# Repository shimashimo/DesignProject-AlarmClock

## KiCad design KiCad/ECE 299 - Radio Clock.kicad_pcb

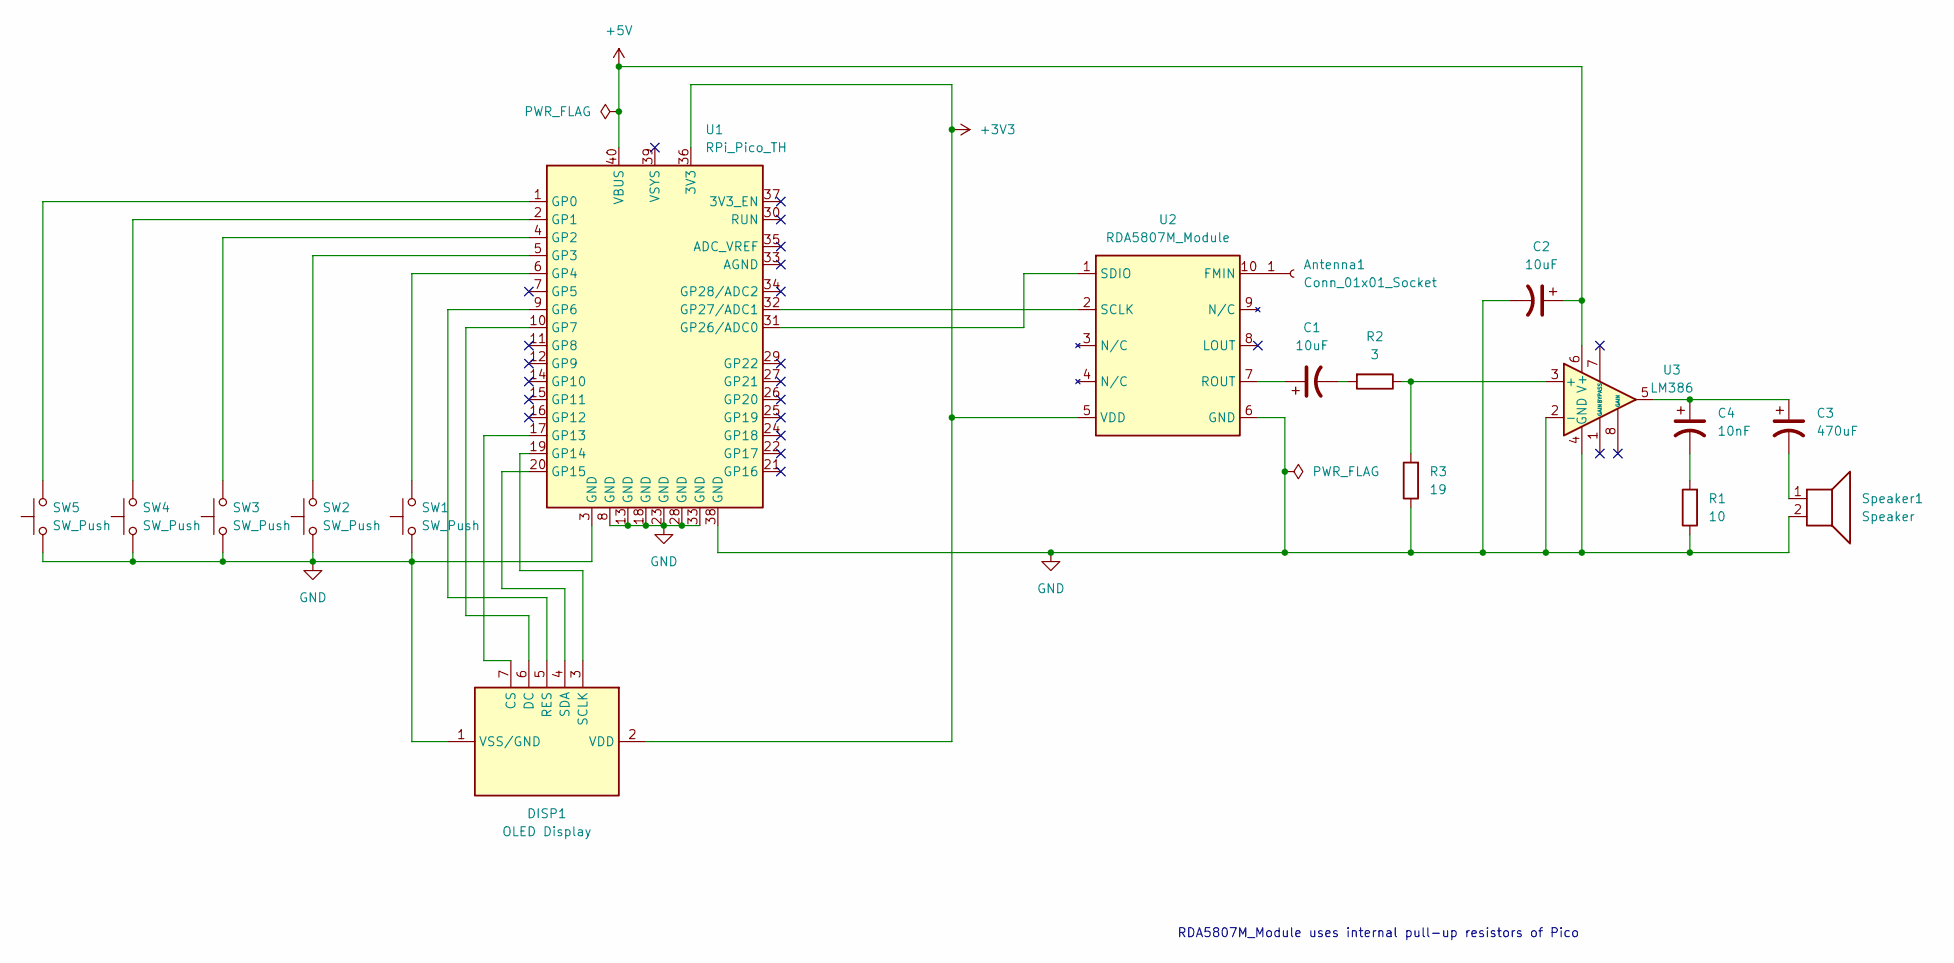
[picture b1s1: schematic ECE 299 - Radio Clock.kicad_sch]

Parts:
Antenna1: Conn_01x01_Socket; PinSocket_1x01_P1.27mm_Vertical
C1, C2: 10uF; CP_Radial_D6.3mm_P2.50mm
C3: 470uF; CP_Radial_D6.3mm_P2.50mm
C4: 10nF; C_Axial_L3.8mm_D2.6mm_P7.50mm_Horizontal
DISP1: OLED Display; OLED_Display_1.3
R1: 10; R_Axial_DIN0207_L6.3mm_D2.5mm_P10.16mm_Horizontal
R2: 3; R_Axial_DIN0207_L6.3mm_D2.5mm_P10.16mm_Horizontal
R3: 19; R_Axial_DIN0207_L6.3mm_D2.5mm_P10.16mm_Horizontal
SW1, SW2, SW3, SW4, SW5: SW_Push; SW_PUSH_6mm
Speaker1: Speaker; TerminalBlock_Phoenix_MKDS-1,5-2_1x02_P5.00mm_Horizontal
U1: RPi_Pico_TH
U2: RDA5807M_Module; RDA5807M_Module_TH
U3: LM386; DIP-8_W7.62mm

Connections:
+3V3: DISP1.2 (VDD), U1.36 (3V3), U2.5 (VDD)
+5V: C2.1, U1.40 (VBUS), U3.6 (V+)
GND: C2.2, DISP1.1 (VSS/GND), R1.1, R3.1, SW1.1, SW2.1, SW3.1, SW4.1, SW5.1, Speaker1.2, U1.3 (GND), U1.8 (GND), U1.13 (GND), U1.18 (GND), U1.23 (GND), U1.28 (GND), U1.33 (GND), U1.38 (GND), U2.6 (GND), U3.2 (-), U3.4 (GND)
unnamed: Antenna1.1, U2.10 (FMIN)
unnamed: C1.2, R2.2
unnamed: C3.1, C4.1, U3.5
unnamed: C3.2, Speaker1.1
unnamed: C4.2, R1.2
unnamed: DISP1.7 (CS), U1.17 (GP13)
unnamed: DISP1.6 (DC), U1.10 (GP7)
unnamed: DISP1.5 (RES), U1.9 (GP6)
unnamed: DISP1.3 (SCLK), U1.19 (GP14)
unnamed: DISP1.4 (SDA), U1.20 (GP15)
unnamed: SW5.2, U1.1 (GP0)
unnamed: SW4.2, U1.2 (GP1)
unnamed: SW3.2, U1.4 (GP2)
unnamed: SW2.2, U1.5 (GP3)
unnamed: SW1.2, U1.6 (GP4)
unnamed: U1.31 (GP26/ADC0), U2.1 (SDIO)
unnamed: U1.32 (GP27/ADC1), U2.2 (SCLK)
unnamed: C1.1, U2.7 (ROUT)
unnamed: R2.1, R3.2, U3.3 (+)

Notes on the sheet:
RDA5807M_Module uses internal pull-up resistors of Pico

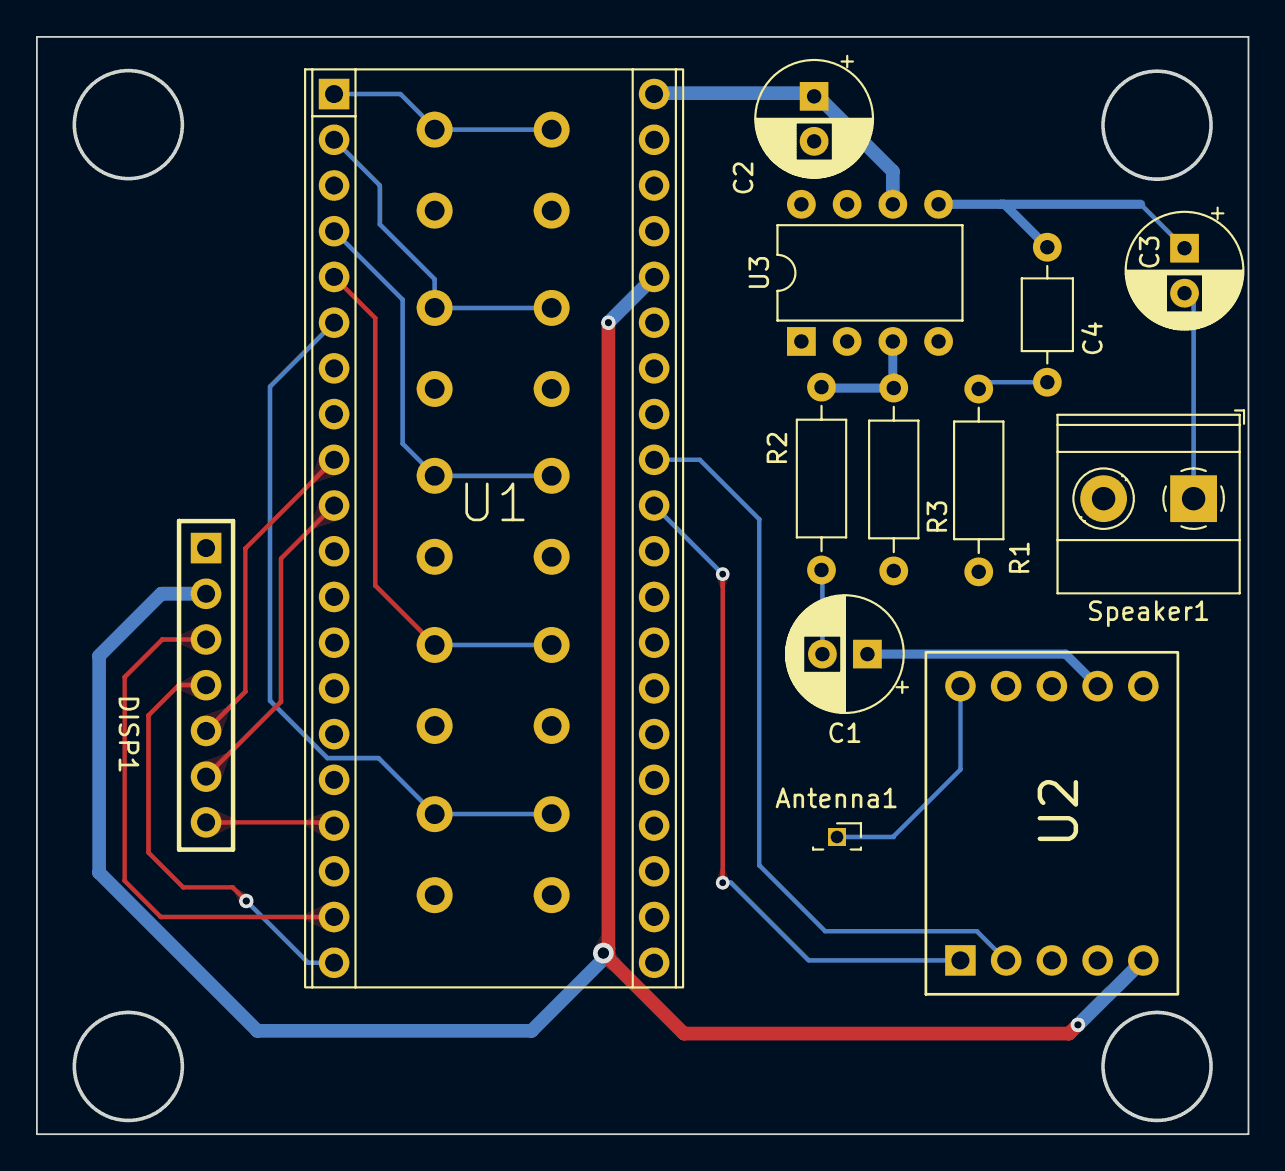
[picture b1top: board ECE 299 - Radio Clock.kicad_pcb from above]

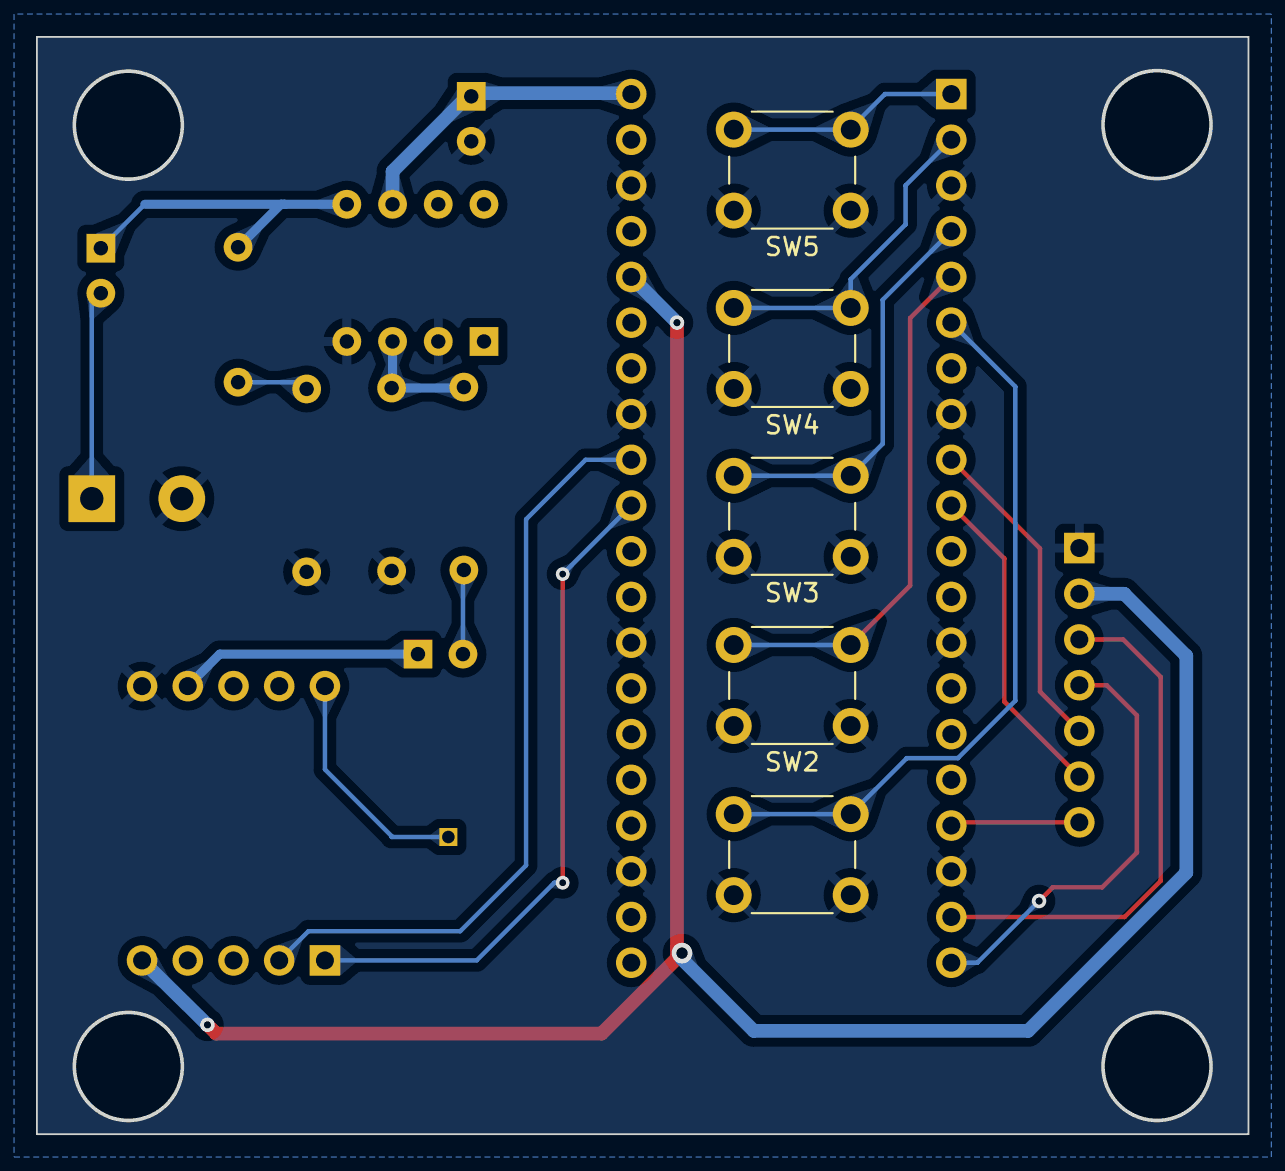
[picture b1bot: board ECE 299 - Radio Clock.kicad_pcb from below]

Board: 2 copper layers, 67.2 x 60.9 mm, 18 parts (5 on the bottom side), 22 nets.

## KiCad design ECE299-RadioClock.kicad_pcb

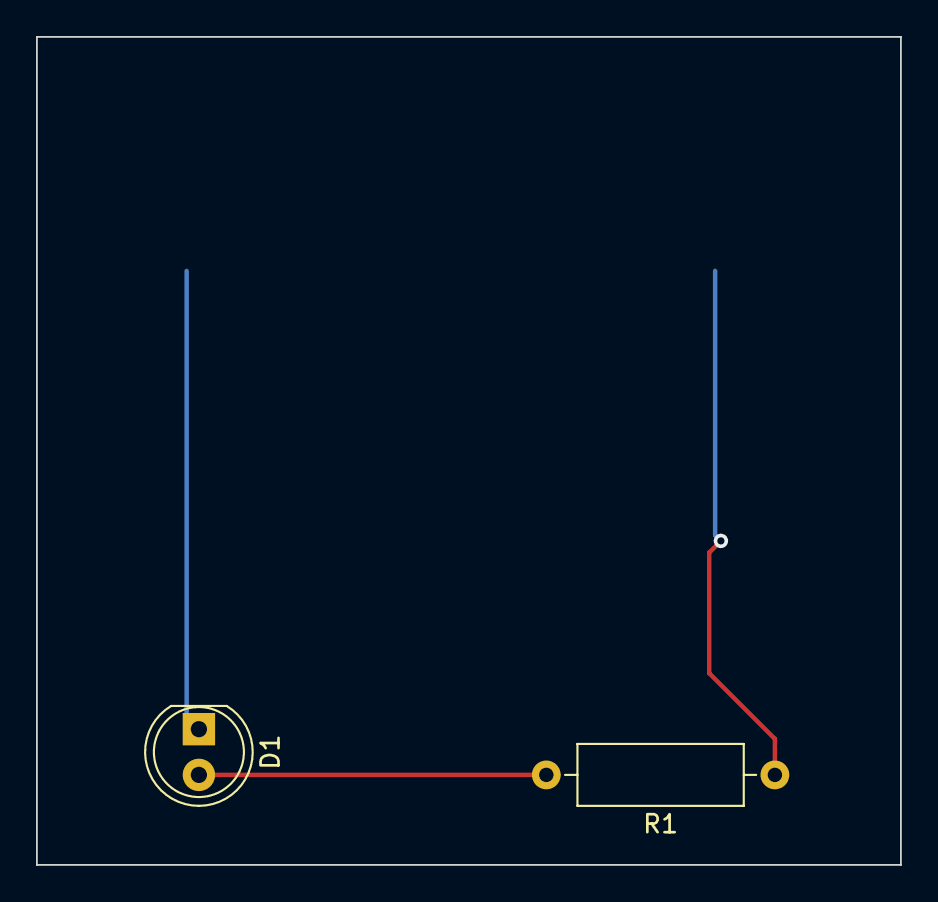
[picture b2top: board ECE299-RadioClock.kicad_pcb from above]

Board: 2 copper layers, 48.0 x 46.0 mm, 3 parts (1 on the bottom side), 3 nets.

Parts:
BT1: 3V; BatteryHolder_Keystone_1058_1x2032
D1: RED; LED_D5.0mm
R1: 1k; R_Axial_DIN0309_L9.0mm_D3.2mm_P12.70mm_Horizontal

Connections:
/led: D1.2 (A), R1.2
GND: BT1.2 (-), D1.1 (K)
VCC: BT1.1 (+), R1.1

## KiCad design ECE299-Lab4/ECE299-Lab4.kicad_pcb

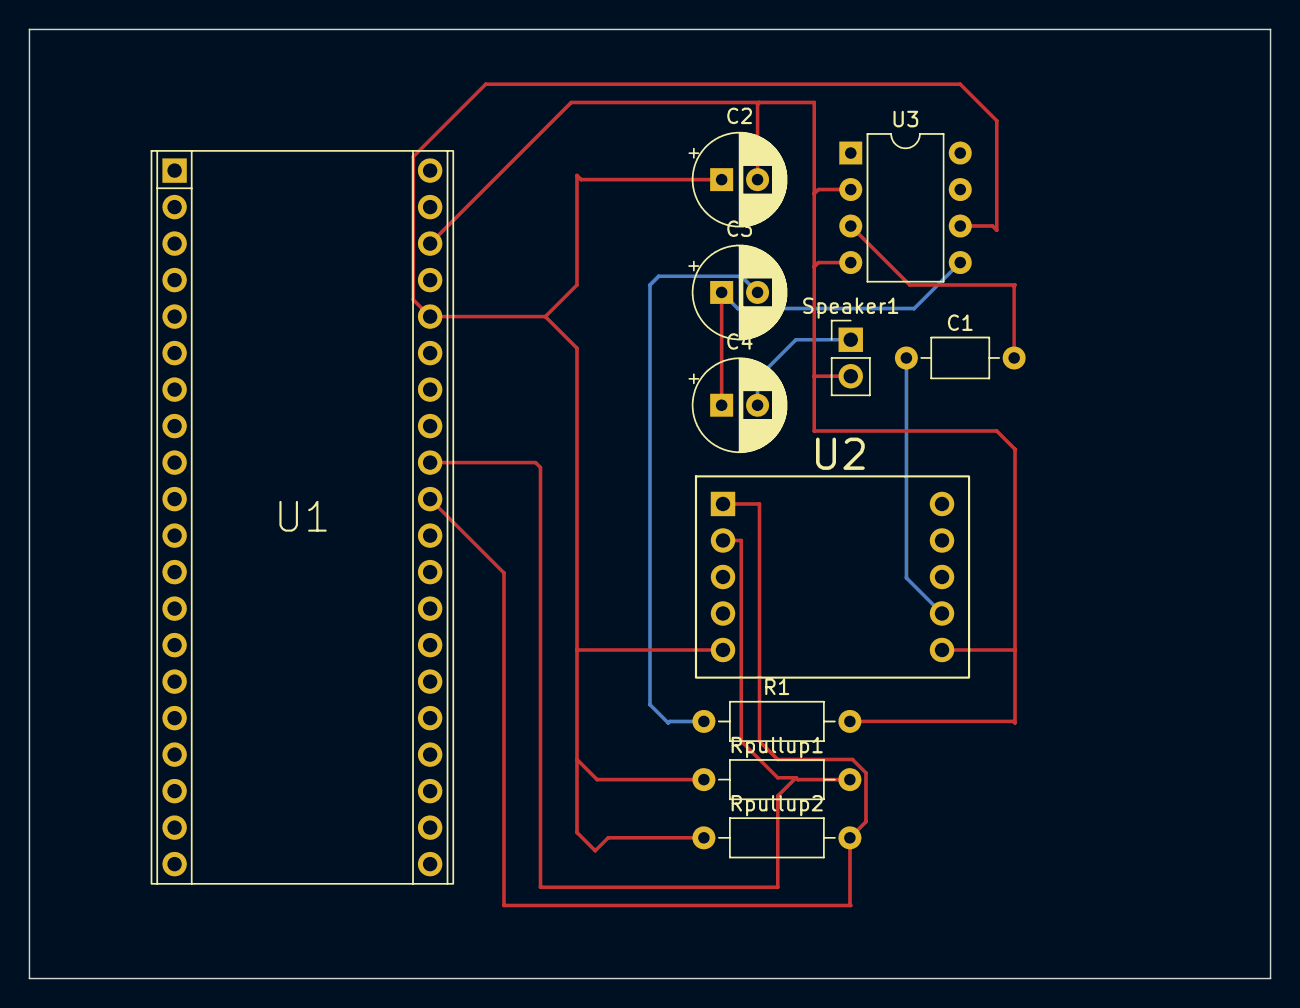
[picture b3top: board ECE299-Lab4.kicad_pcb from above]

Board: 2 copper layers, 86.4 x 66.0 mm, 11 parts (0 on the bottom side), 9 nets.

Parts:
C1: 10nF; C_Axial_L3.8mm_D2.6mm_P7.50mm_Horizontal
C2, C3: 10uF; CP_Radial_D6.3mm_P2.50mm
C4: 470uF; CP_Radial_D6.3mm_P2.50mm
R1: 10; R_Axial_DIN0207_L6.3mm_D2.5mm_P10.16mm_Horizontal
Rpullup1, Rpullup2: 2k; R_Axial_DIN0207_L6.3mm_D2.5mm_P10.16mm_Horizontal
Speaker1: 8; PinHeader_1x02_P2.54mm_Vertical
U1: RPi_Pico_TH
U2: RDA5807M_Module; RDA5807M_Module_TH
U3: LM386; DIP-8_W7.62mm

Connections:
+3.3V: C2.1, Rpullup1.1, Rpullup2.1, U1.36 (3V3), U2.5 (VDD), U3.6 (V+)
GND: C2.2, R1.2, Speaker1.2, U1.38 (GND), U2.6 (GND), U3.2 (-), U3.4 (GND)
unnamed: C3.1, C4.1, U3.5
unnamed: C3.2, R1.1
unnamed: C4.2, Speaker1.1
unnamed: Rpullup2.2, U1.31 (GP26/ADC0), U2.1 (SDIO)
unnamed: Rpullup1.2, U1.32 (GP27/ADC1), U2.2 (SCLK)
unnamed: C1.1, U2.7 (ROUT)
unnamed: C1.2, U3.3 (+)

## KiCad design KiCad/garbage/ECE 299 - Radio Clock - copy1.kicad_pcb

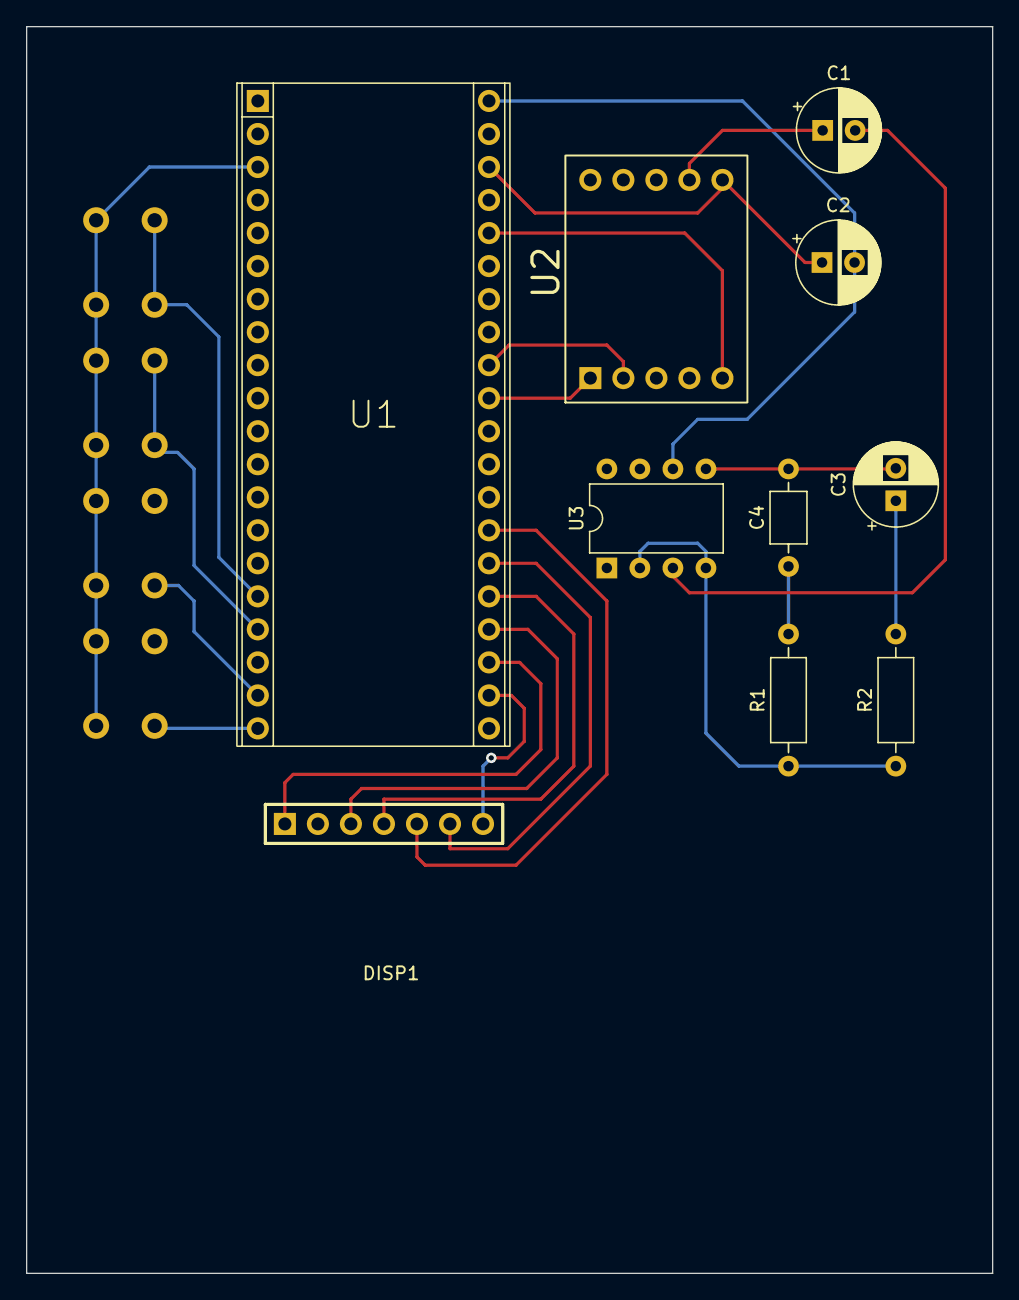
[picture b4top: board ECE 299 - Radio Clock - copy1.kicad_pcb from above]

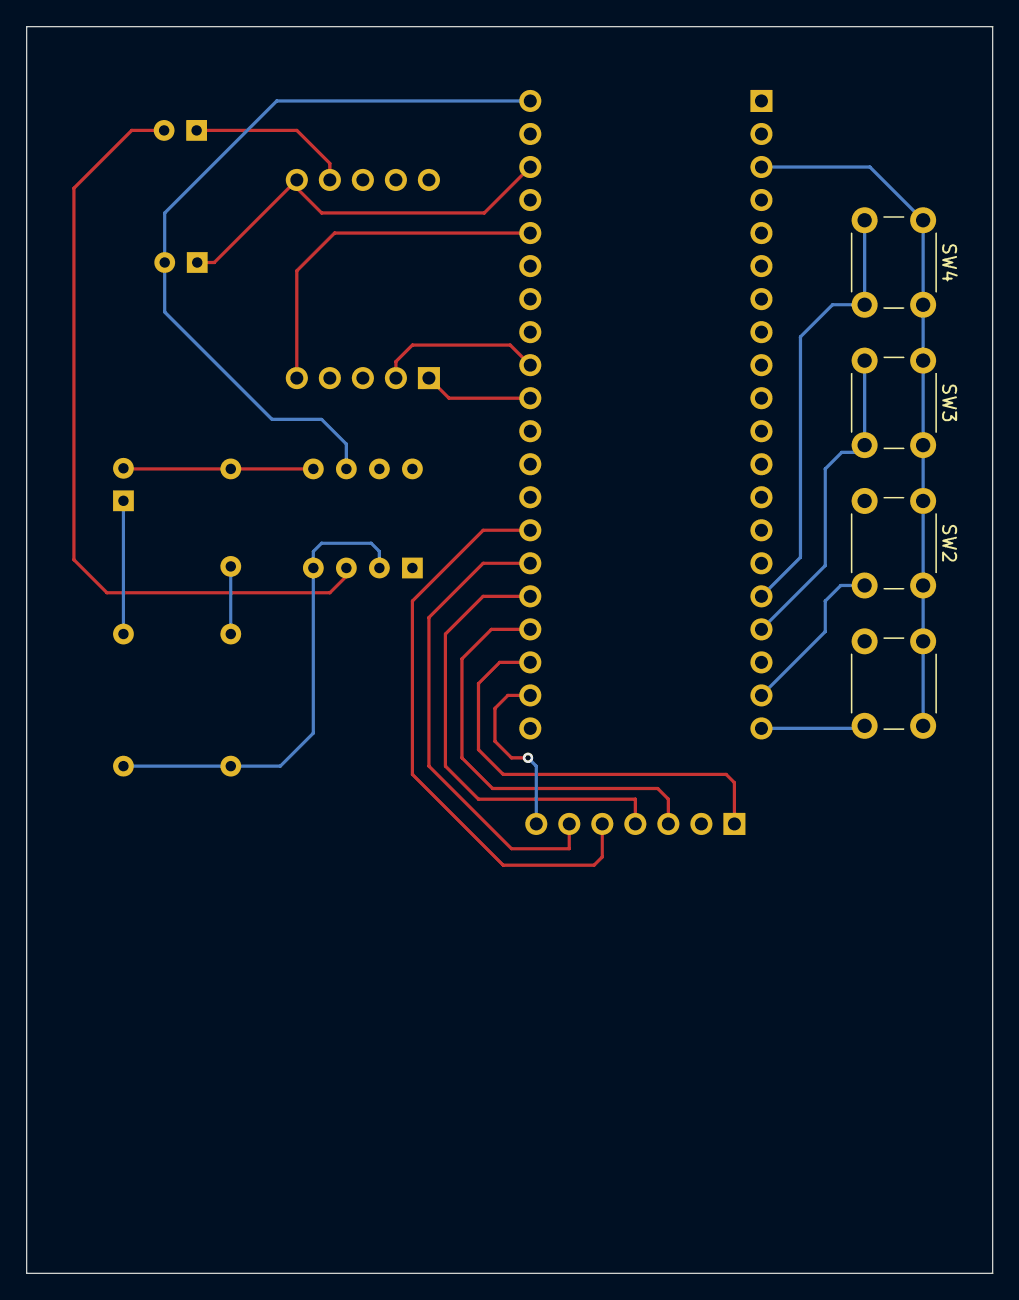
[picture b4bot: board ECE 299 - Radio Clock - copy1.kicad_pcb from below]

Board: 2 copper layers, 74.3 x 95.9 mm, 14 parts (4 on the bottom side), 18 nets.

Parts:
C1, C2: 10uF; CP_Radial_D6.3mm_P2.50mm
C3: 470uF; CP_Radial_D6.3mm_P2.50mm
C4: 10nF; C_Axial_L3.8mm_D2.6mm_P7.50mm_Horizontal
DISP1: OLED Display; OLED_Display_1.3
R1: 10; R_Axial_DIN0207_L6.3mm_D2.5mm_P10.16mm_Horizontal
R2: 8; R_Axial_DIN0207_L6.3mm_D2.5mm_P10.16mm_Horizontal
SW1, SW2, SW3, SW4: SW_Push; SW_PUSH_6mm
U1: RPi_Pico_TH
U2: RDA5807M_Module; RDA5807M_Module_TH
U3: LM386; DIP-8_W7.62mm

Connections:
GND: C2.1, DISP1.1 (VSS/GND), R1.1, R2.1, SW1.1, SW2.1, SW3.1, SW4.1, U1.3 (GND), U1.23 (GND), U1.38 (GND), U2.6 (GND), U3.2 (-), U3.4 (GND)
unnamed: C3.1, R2.2
unnamed: C3.2, C4.2, U3.5
unnamed: C4.1, R1.2
unnamed: DISP1.7 (CS), U1.22 (GP17)
unnamed: DISP1.6 (DC), U1.26 (GP20)
unnamed: DISP1.5 (RES), U1.27 (GP21)
unnamed: DISP1.3 (SCLK), U1.24 (GP18)
unnamed: DISP1.4 (SDA), U1.25 (GP19)
unnamed: SW4.2, U1.16 (GP12)
unnamed: SW3.2, U1.17 (GP13)
unnamed: SW2.2, U1.19 (GP14)
unnamed: SW1.2, U1.20 (GP15)
unnamed: U1.31 (GP26/ADC0), U2.1 (SDIO)
unnamed: U1.32 (GP27/ADC1), U2.2 (SCLK)
unnamed: C1.1, U2.7 (ROUT)
unnamed: C1.2, U3.3 (+)
VCC: C2.2, DISP1.2 (VDD), U1.36 (3V3), U1.40 (VBUS), U2.5 (VDD), U3.6 (V+)

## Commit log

2023-06-10 Initial Commit - Completed Code for Lab 1 and 2
2023-06-10 Completed Code for Labs 2 and 3
2023-06-28 24 Hour to AM PM format working and switchable
2023-06-28 Finished 24 to 12 hour formt and added AM/PM
2023-06-28 Commiting Schematics and PCB stuff
2023-07-18 changed basicdisplay name to main
2023-07-18 Updated and renamed main file from 'basicdisplay.py' to 'main.py'
2023-07-19 KiCad files weren't manually changed, but needed to be committed? Radio and RadioClass were also not touched.
2023-07-19 Tried using PWM for alarm sound. It works but probably won't use
2023-07-24 Added functions files to repo
2023-07-24 Fixed merge conflicts and returned to vanilla radio file that works for our pico
2023-07-24 Resolving merge conflicts
2023-07-24 Created Radio class functions to increase and decrease time
2023-07-24 Adding read and write register testing file.
2023-07-24 Testing more register bits
2023-07-28 Final code used in demo
2023-07-28 Added default display tester file and KiCad backups updated
2023-08-04 Adding basicdisplay.py file given by school
